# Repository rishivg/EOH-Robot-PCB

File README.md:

# EOH-Robot-PCB
EOH Robot PCB boards

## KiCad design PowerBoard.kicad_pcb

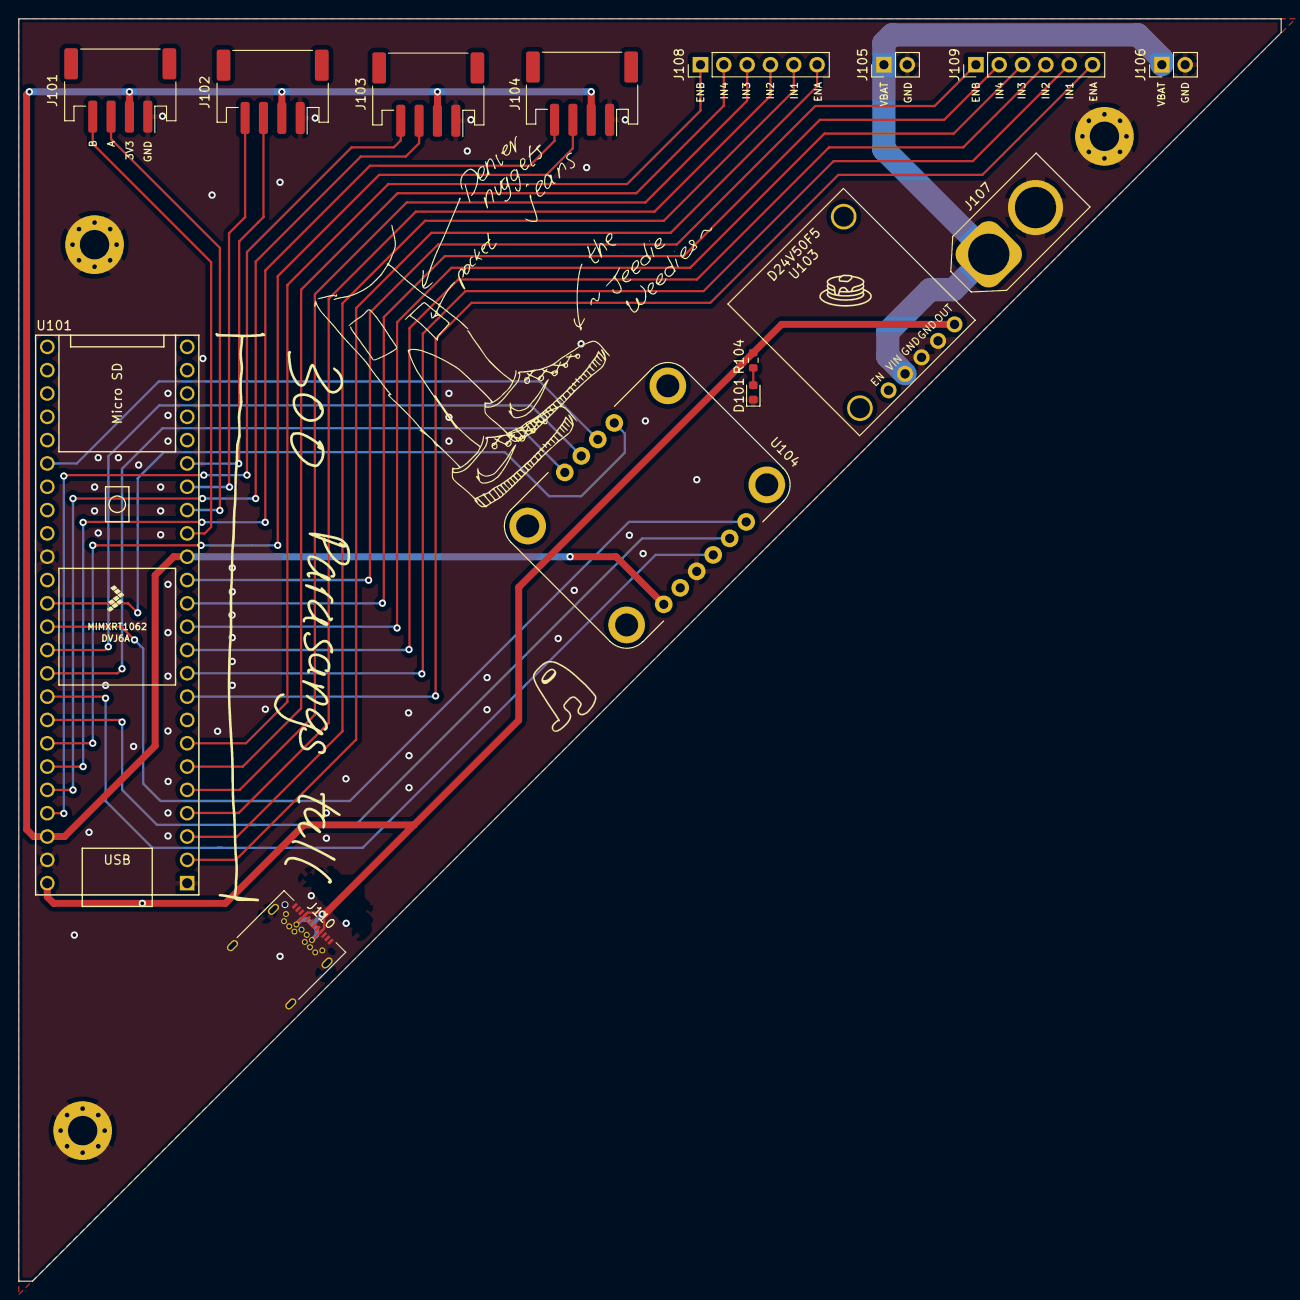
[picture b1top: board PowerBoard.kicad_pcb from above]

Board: 2 copper layers, 137.5 x 137.5 mm, 18 parts (0 on the bottom side), 32 nets.

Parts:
D101: LED; LED_0603_1608Metric
H1, H2, H3: MountingHole_Pad; MountingHole_3.2mm_M3_Pad_Via
J101, J102, J103, J104: Conn_01x04_Pin; JST_PH_S4B-PH-SM4-TB_1x04-1MP_P2.00mm_Horizontal
J105, J106: Conn_01x02_Pin; PinHeader_1x02_P2.54mm_Vertical
J107: Conn_01x02_Pin; AMASS_XT60-M_1x02_P7.20mm_Vertical
J108, J109: Conn_01x06_Pin; PinHeader_1x06_P2.54mm_Vertical
J110: USB_C_Receptacle; USB_C_Receptacle_Amphenol_12401548E4-2A
R104: 1k; R_0603_1608Metric
U101: Teensy4.1; Teensy41_bare_pins
U103: D24V50F5
U104: 2472; MODULE_2472

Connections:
3V3: J101.2, J102.2, J103.2, J104.2, U101.15 (3V3), U101.46 (3V3), U104.1 (VIN)
5V: J110.A4 (VBUS), J110.A9 (VBUS), J110.B4 (VBUS), J110.B9 (VBUS), R104.1, U101.48 (VIN), U103.5 (OUT)
/BNO_INT: U101.30 (38_CS1_IN1), U104.8 (INT)
/IMU_ADR: U101.36 (14_A0_TX3_SPDIF_OUT), U104.7 (ADR)
/IMU_PS0: U101.39 (17_A3_TX4_SDA1), U104.10 (PS0)
/IMU_PS1: U101.38 (16_A2_RX4_SCL1), U104.9 (PS1)
/IMU_RST: U101.37 (15_A1_RX3_SPDIF_IN), U104.6 (RST)
/IMU_SCL: U101.41 (19_A5_SCL), U104.5 (SCL)
/IMU_SDA: U101.40 (18_A4_SDA), U104.4 (SDA)
/L298N1_ENA: J108.6, U101.2 (0_RX1_CRX2_CS1)
/L298N1_ENB: J108.1, U101.7 (5_IN2)
/L298N1_IN1: J108.5, U101.3 (1_TX1_CTX2_MISO1)
/L298N1_IN2: J108.4, U101.4 (2_OUT2)
/L298N1_IN3: J108.3, U101.5 (3_LRCLK2)
/L298N1_IN4: J108.2, U101.6 (4_BCLK2)
/L298N2_ENA: J109.6, U101.9 (7_RX2_OUT1A)
/L298N2_ENB: J109.1, U101.14 (12_MISO_MQSL)
/L298N2_IN1: J109.5, U101.10 (8_TX2_IN1)
/L298N2_IN2: J109.4, U101.11 (9_OUT1C)
/L298N2_IN3: J109.3, U101.12 (10_CS_MQSR)
/L298N2_IN4: J109.2, U101.13 (11_MOSI_CTX1)
/Motor1_A: J101.3, U101.17 (25_A11_RX6_SDA2)
/Motor1_B: J101.4, U101.16 (24_A10_TX6_SCL2)
/Motor2_A: J102.3, U101.19 (27_A13_SCK1)
/Motor2_B: J102.4, U101.18 (26_A12_MOSI1)
/Motor3_A: J103.3, U101.44 (22_A8_CTX1)
/Motor3_B: J103.4, U101.45 (23_A9_CRX1_MCLK1)
/Motor4_A: J104.3, U101.42 (20_A6_TX5_LRCLK1)
/Motor4_B: J104.4, U101.43 (21_A7_RX5_BCLK1)
GND: D101.1 (K), H1.1, H2.1, H3.1, J101.1, J102.1, J103.1, J104.1, J105.2, J106.2, J107.2, J110.A1 (GND), J110.A12 (GND), J110.B1 (GND), J110.B12 (GND), J110.S1 (SHIELD), U101.1 (GND), U101.34 (GND), U101.47 (GND), U103.3 (GND), U103.4 (GND), U104.3 (GND)
unnamed: D101.2 (A), R104.2
VIN: J105.1, J106.1, J107.1, U103.2 (VIN)

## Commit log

2024-02-21 Added progress so far
    Added progress so far
2024-02-21 weedies
    weedies
2024-02-25 Big Moves
    Big Moves
2024-02-26 some small routing touchups
    made power traces much larger, made battery connector GND pad thermal reliefs larger, organized trace spacing a bit more, deleted some vias that didn't add anything, added a 15mil keepout around the 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
2024-02-29 ready for review
    Flipped encoder connector pinout, added mounting holes, fixed battery connector footprint, moved USB C connector, added memes, added placeholder names
2024-02-29 only need names
    should be ready to order the board once we get list of names for back silkscreen
2024-02-29 ready to order
    added more memes and updated name list
2024-12-11 Create LICENSE
